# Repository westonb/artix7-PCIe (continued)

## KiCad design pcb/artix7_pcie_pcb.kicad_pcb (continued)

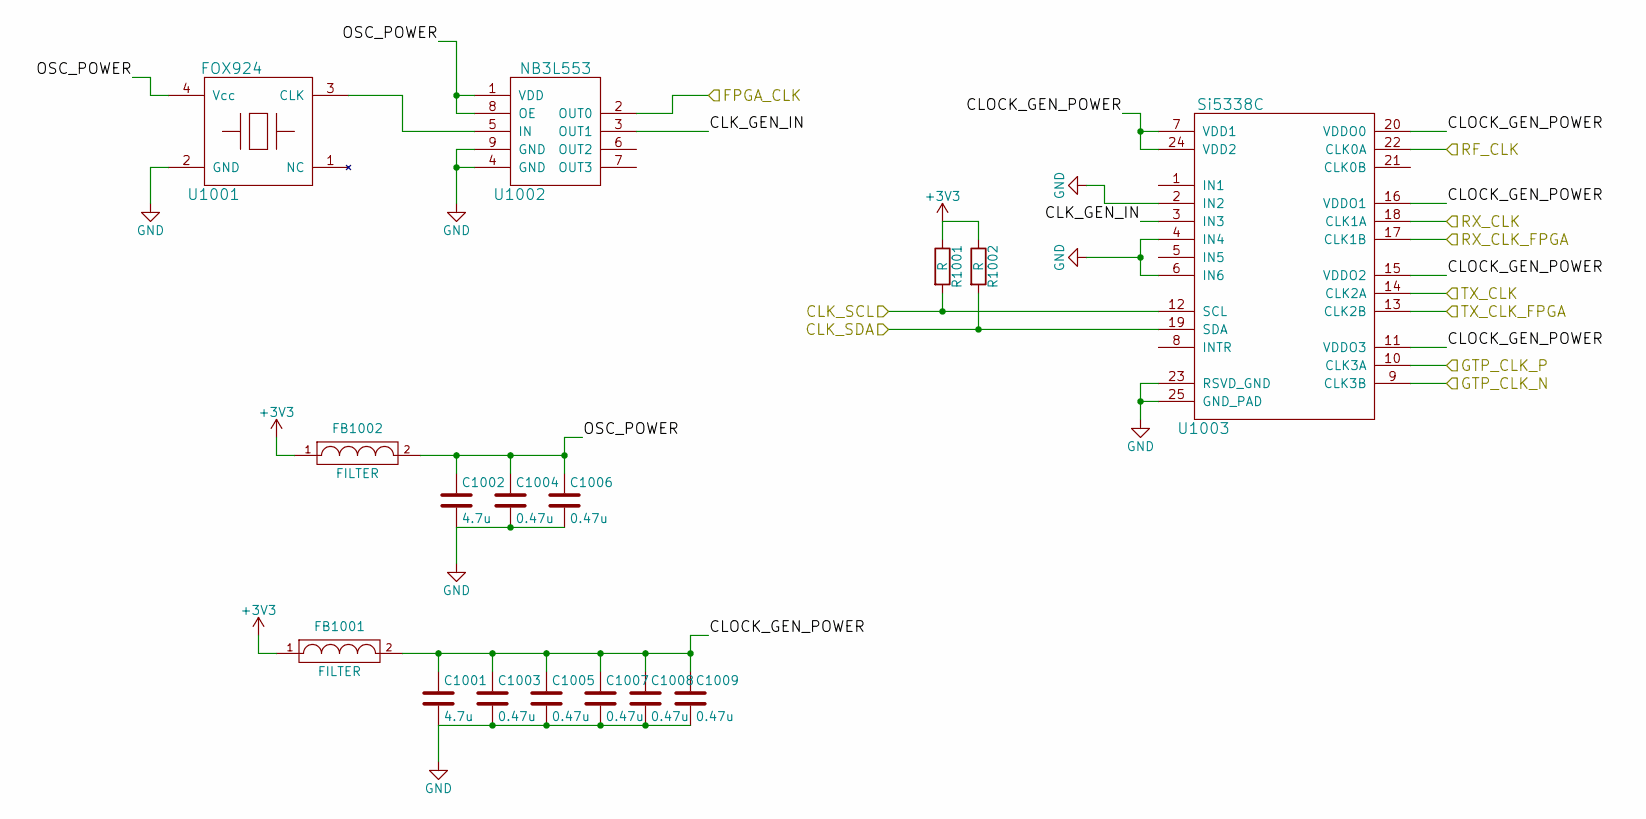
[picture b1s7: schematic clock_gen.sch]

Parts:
C1001, C1002: 4.7u; C_0402
C1003, C1004, C1005, C1006, C1007, C1008, C1009: 0.47u; C_0402
FB1001, FB1002: FILTER; L_0603
R1001, R1002: R; R_0402
U1001: FOX924; OSCILLATOR_5.0X3.2
U1002: NB3L553; DFN-8_2x2mm_Pitch0.5mm
U1003: Si5338C; QFN-24-1EP_4x4mm_Pitch0.5mm

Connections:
+3V3: FB1001.1, FB1002.1, R1001.1, R1002.1; also elsewhere on the board
/Clocking/CLK_GEN_IN: U1002.3 (OUT1), U1003.3 (IN3)
/Clocking/CLK_SCL: R1001.2, U1003.12 (SCL); also elsewhere on the board
/Clocking/CLK_SDA: R1002.2, U1003.19 (SDA); also elsewhere on the board
/Clocking/CLOCK_GEN_POWER: C1001.1, C1003.1, C1005.1, C1007.1, C1008.1, C1009.1, FB1001.2, U1003.7 (VDD1), U1003.11 (VDDO3), U1003.15 (VDDO2), U1003.16 (VDDO1), U1003.20 (VDDO0), U1003.24 (VDD2)
/Clocking/FPGA_CLK: U1002.2 (OUT0); also elsewhere on the board
/Clocking/GTP_CLK_N: U1003.9 (CLK3B); also elsewhere on the board
/Clocking/GTP_CLK_P: U1003.10 (CLK3A); also elsewhere on the board
/Clocking/OSC_POWER: C1002.1, C1004.1, C1006.1, FB1002.2, U1001.4 (Vcc), U1002.1 (VDD), U1002.8 (OE)
/Clocking/RF_CLK: U1003.22 (CLK0A); also elsewhere on the board
/Clocking/RX_CLK: U1003.18 (CLK1A); also elsewhere on the board
/Clocking/RX_CLK_FPGA: U1003.17 (CLK1B); also elsewhere on the board
/Clocking/TX_CLK: U1003.14 (CLK2A); also elsewhere on the board
/Clocking/TX_CLK_FPGA: U1003.13 (CLK2B); also elsewhere on the board
GND: C1001.2, C1002.2, C1003.2, C1004.2, C1005.2, C1006.2, C1007.2, C1008.2, C1009.2, U1001.2 (GND), U1002.4 (GND), U1002.9 (GND), U1003.2 (IN2), U1003.4 (IN4), U1003.6 (IN6), U1003.23 (RSVD_GND), U1003.25 (GND_PAD); also elsewhere on the board
unnamed: U1001.3 (CLK), U1002.5 (IN)

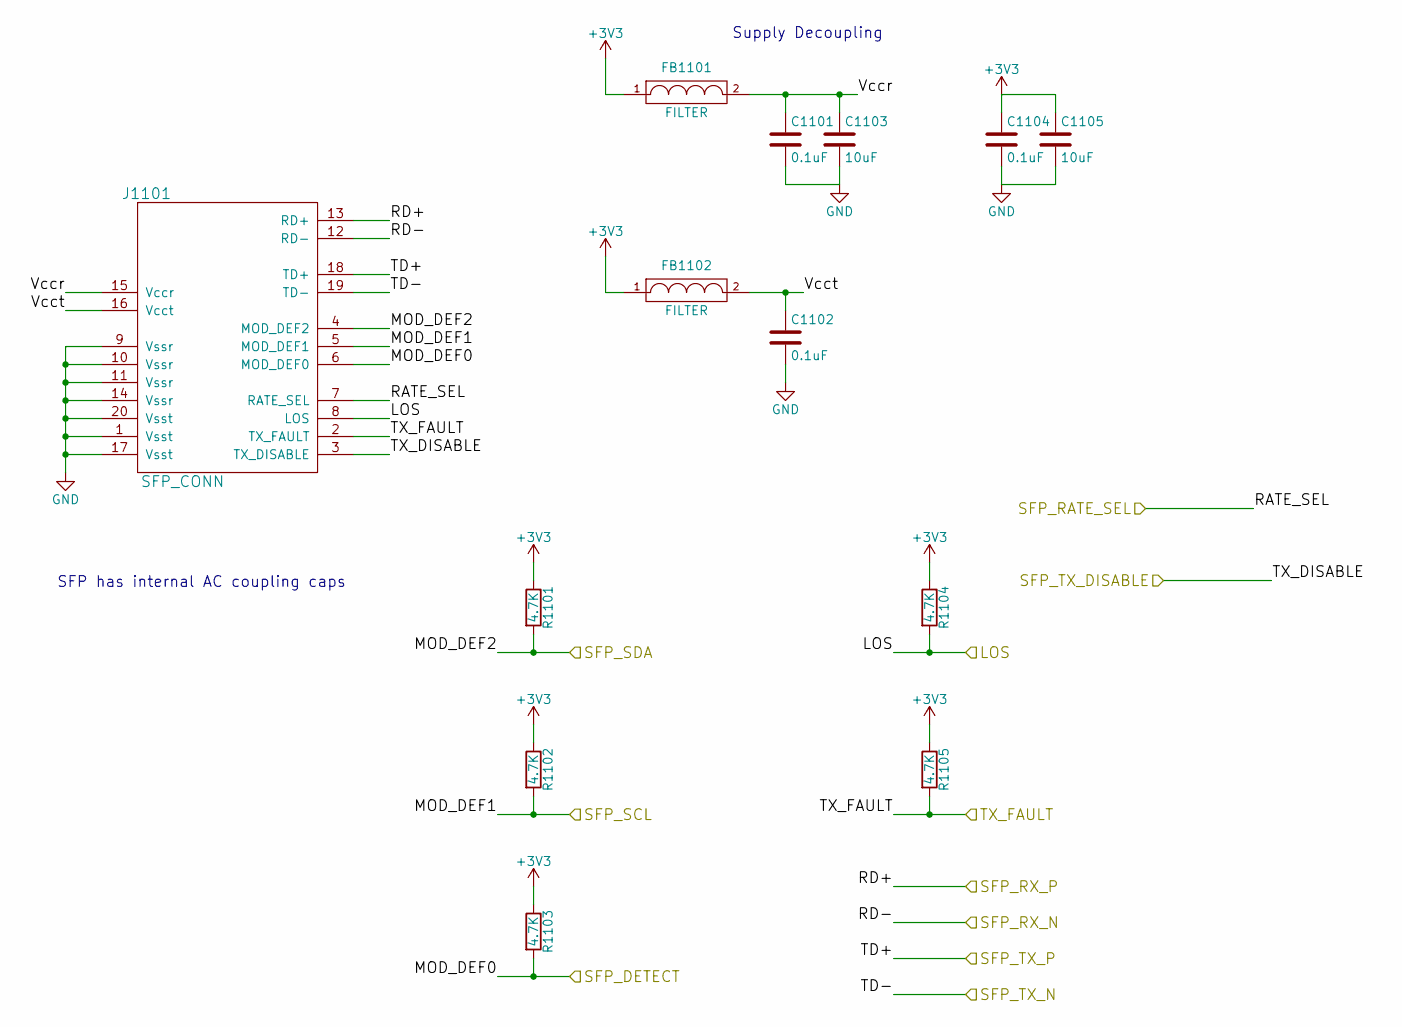
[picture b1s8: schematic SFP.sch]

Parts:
C1101, C1102, C1104: 0.1uF; C_0402
C1103, C1105: 10uF; C_0402
FB1101, FB1102: FILTER; L_0603
J1101: SFP_CONN; CONN-SFP_1367073-1
R1101, R1102, R1103, R1104, R1105: 4.7K; R_0402

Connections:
+3V3: C1104.1, C1105.1, FB1101.1, FB1102.1, R1101.1, R1102.1, R1103.1, R1104.1, R1105.1; also elsewhere on the board
/FPGA Transceivers/SFP_RX_N: J1101.12 (RD-); also elsewhere on the board
/FPGA Transceivers/SFP_RX_P: J1101.13 (RD+); also elsewhere on the board
/FPGA Transceivers/SFP_TX_N: J1101.19 (TD-); also elsewhere on the board
/FPGA Transceivers/SFP_TX_P: J1101.18 (TD+); also elsewhere on the board
/MyriadRF IO/SFP_DETECT: J1101.6 (MOD_DEF0), R1103.2; also elsewhere on the board
/MyriadRF IO/SFP_RATE_SEL: J1101.7 (RATE_SEL); also elsewhere on the board
/MyriadRF IO/SFP_SCL: J1101.5 (MOD_DEF1), R1102.2; also elsewhere on the board
/MyriadRF IO/SFP_SDA: J1101.4 (MOD_DEF2), R1101.2; also elsewhere on the board
/MyriadRF IO/SFP_TX_DISABLE: J1101.3 (TX_DISABLE); also elsewhere on the board
/MyriadRF IO/SFP_TX_FAULT: J1101.2 (TX_FAULT), R1105.2; also elsewhere on the board
/SFP/LOS: J1101.8 (LOS), R1104.2; also elsewhere on the board
/SFP/Vccr: C1101.1, C1103.1, FB1101.2, J1101.15 (Vccr)
/SFP/Vcct: C1102.1, FB1102.2, J1101.16 (Vcct)
GND: C1101.2, C1102.2, C1103.2, C1104.2, C1105.2, J1101.1 (Vsst), J1101.9 (Vssr), J1101.10 (Vssr), J1101.11 (Vssr), J1101.14 (Vssr), J1101.17 (Vsst), J1101.20 (Vsst); also elsewhere on the board

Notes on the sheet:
Supply Decoupling
SFP has internal AC coupling caps

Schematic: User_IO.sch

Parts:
D1201, D1202, D1203, D1204: LED; LED-0805
P1201, P1202: CONN_02X05; Pin_Header_Straight_2x05
R1201, R1202, R1203, R1204, R1207, R1208: R; R_0402
SW1201, SW1202: SW_PUSH; button-5mm
U401: XC7Axxt-FGG484; BGA_484_22x22_FULLARRAY_1MM

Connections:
+3V3: P1201.9, P1202.9, R1207.2, R1208.2; also elsewhere on the board
/User IO/B0: R1208.1, SW1202.1, U401.T1 (IO_L1P_T0_34)
/User IO/B1: R1207.1, SW1201.1, U401.U1 (IO_L1N_T0_34)
/User IO/IO0: P1201.1, U401.V4 (IO_L12P_T1_MRCC_34)
/User IO/IO1: P1201.2, U401.AA4 (IO_L11N_T1_SRCC_34)
/User IO/IO2: P1201.3, U401.Y4 (IO_L11P_T1_SRCC_34)
/User IO/IO3: P1201.4, U401.W4 (IO_L12N_T1_MRCC_34)
/User IO/IO4: P1201.5, U401.AB3 (IO_L8P_T1_34)
/User IO/IO5: P1201.6, U401.AA3 (IO_L9N_T1_DQS_34)
/User IO/IO6: P1201.7, U401.Y3 (IO_L9P_T1_DQS_34)
/User IO/IO7: P1201.8, U401.AB2 (IO_L8N_T1_34)
/User IO/IO8: P1202.1, U401.R4 (IO_L13P_T2_MRCC_34)
/User IO/IO9: P1202.2, U401.R3 (IO_L3P_T0_DQS_34)
/User IO/IO10: P1202.3, U401.AB1 (IO_L7N_T1_34)
/User IO/IO11: P1202.4, U401.AA1 (IO_L7P_T1_34)
/User IO/IO12: P1202.5, U401.Y2 (IO_L4N_T0_34)
/User IO/IO13: P1202.6, U401.Y1 (IO_L5N_T0_34)
/User IO/IO14: P1202.7, U401.W2 (IO_L4P_T0_34)
/User IO/IO15: P1202.8, U401.W1 (IO_L5P_T0_34)
/User IO/LED0: R1201.2, U401.U2 (IO_L2P_T0_34)
/User IO/LED1: R1202.2, U401.V2 (IO_L2N_T0_34)
/User IO/LED2: R1203.2, U401.U3 (IO_L6P_T0_34)
/User IO/LED3: R1204.2, U401.V3 (IO_L6N_T0_VREF_34)
/User IO/PCIE_PERST: U401.R6 (IO_L17P_T2_34); also elsewhere on the board
GND: D1201.1 (K), D1202.1 (K), D1203.1 (K), D1204.1 (K), P1201.10, P1202.10, SW1201.2, SW1202.2; also elsewhere on the board
unnamed: D1201.2 (A), R1201.1
unnamed: D1202.2 (A), R1202.1
unnamed: D1203.2 (A), R1203.1
unnamed: D1204.2 (A), R1204.1

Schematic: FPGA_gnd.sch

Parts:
U401: XC7Axxt-FGG484; BGA_484_22x22_FULLARRAY_1MM

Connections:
GND: U401.A2 (GND), U401.A3 (GND), U401.A5 (GND), U401.A7 (GND), U401.A9 (GND), U401.A11 (GND), U401.A12 (GND), U401.A22 (GND), U401.AA2 (GND), U401.AA12 (GND), U401.AA22 (GND), U401.AB9 (GND), U401.AB19 (GND), U401.B3 (GND), U401.B12 (GND), U401.B19 (GND), U401.C3 (GND), U401.C6 (GND), U401.C10 (GND), U401.C12 (GND), U401.C16 (GND), U401.D3 (GND), U401.D4 (GND), U401.D8 (GND), U401.D12 (GND), U401.D13 (GND), U401.E4 (GND), U401.E5 (GND), U401.E7 (GND), U401.E9 (GND), U401.E11 (GND), U401.E20 (GND), U401.F5 (GND), U401.F11 (GND), U401.F17 (GND), U401.G5 (GND), U401.G6 (GND), U401.G7 (GND), U401.G8 (GND), U401.G9 (GND), U401.G10 (GND), U401.G12 (GND), U401.G14 (GND), U401.H1 (GND), U401.H7 (GND), U401.H9 (GND), U401.H11 (GND), U401.H21 (GND), U401.J8 (GND), U401.J10 (GND), U401.J12 (GND), U401.J18 (GND), U401.K5 (GND), U401.K7 (GND), U401.K9 (GNDADC), U401.K11 (GND), U401.K15 (GND), U401.L2 (GND), U401.L8 (GND), U401.L22 (GND), U401.M7 (GND), U401.M11 (GND), U401.M19 (GND), U401.N6 (GND), U401.N8 (GND), U401.N16 (GND), U401.P3 (GND), U401.P7 (GND), U401.P9 (GND), U401.P11 (GND), U401.P13 (GND), U401.R8 (GND), U401.R10 (GND), U401.R12 (GND), U401.R20 (GND), U401.T7 (GND), U401.T9 (GND), U401.T11 (GND), U401.T17 (GND), U401.U4 (GND), U401.U14 (GND), U401.V1 (GND), U401.V11 (GND), U401.V21 (GND), U401.W8 (GND), U401.W18 (GND), U401.Y5 (GND), U401.Y15 (GND); also elsewhere on the board

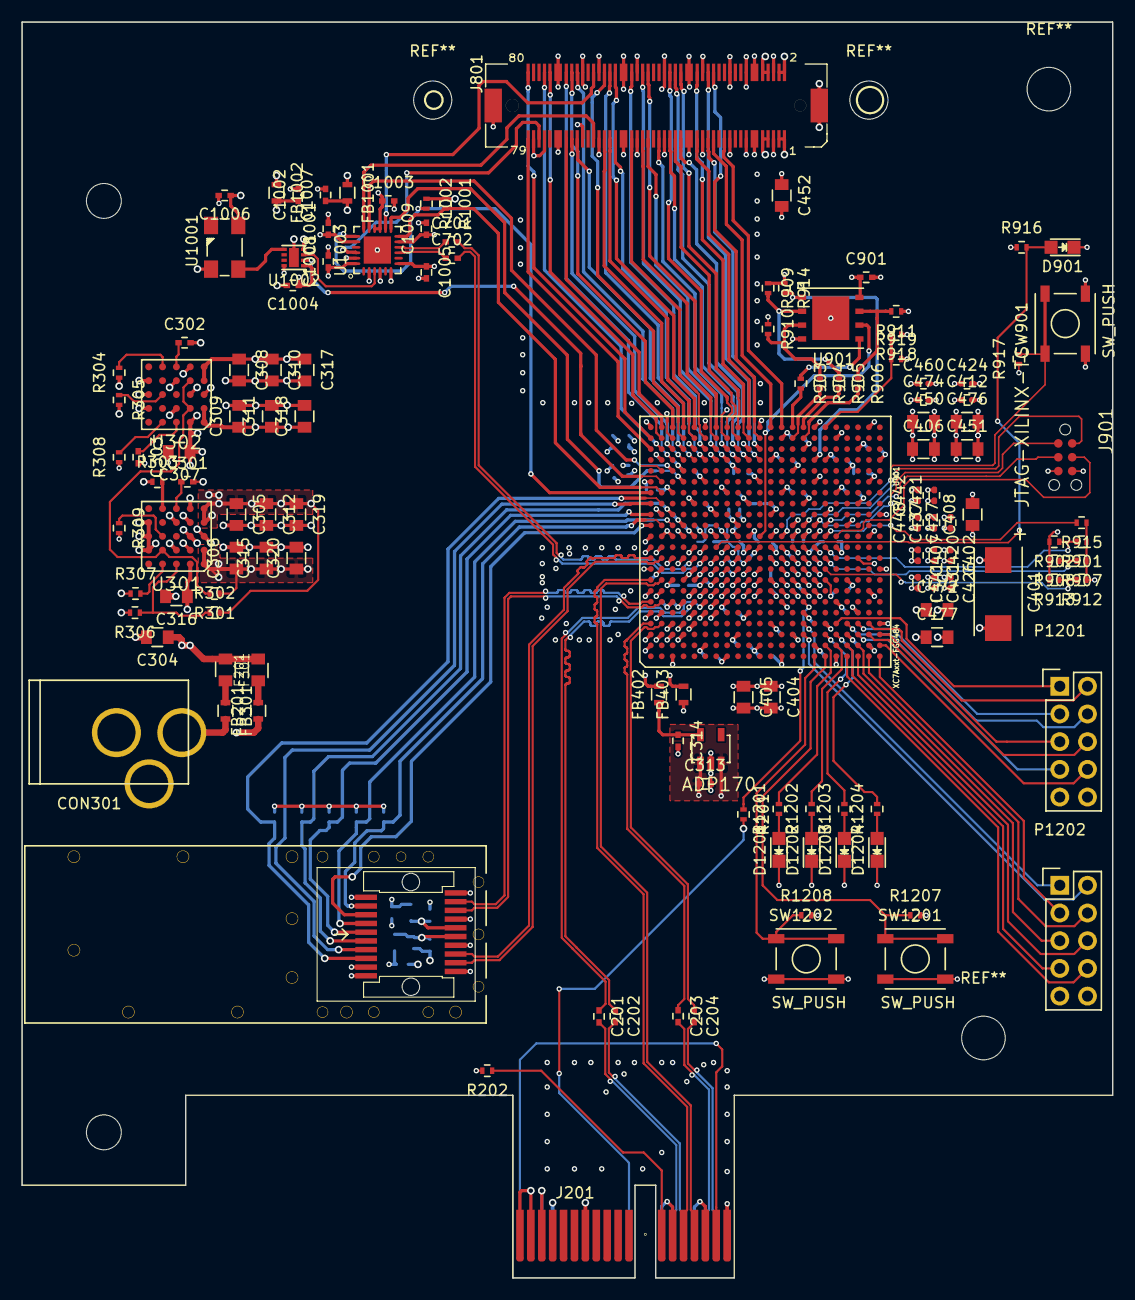
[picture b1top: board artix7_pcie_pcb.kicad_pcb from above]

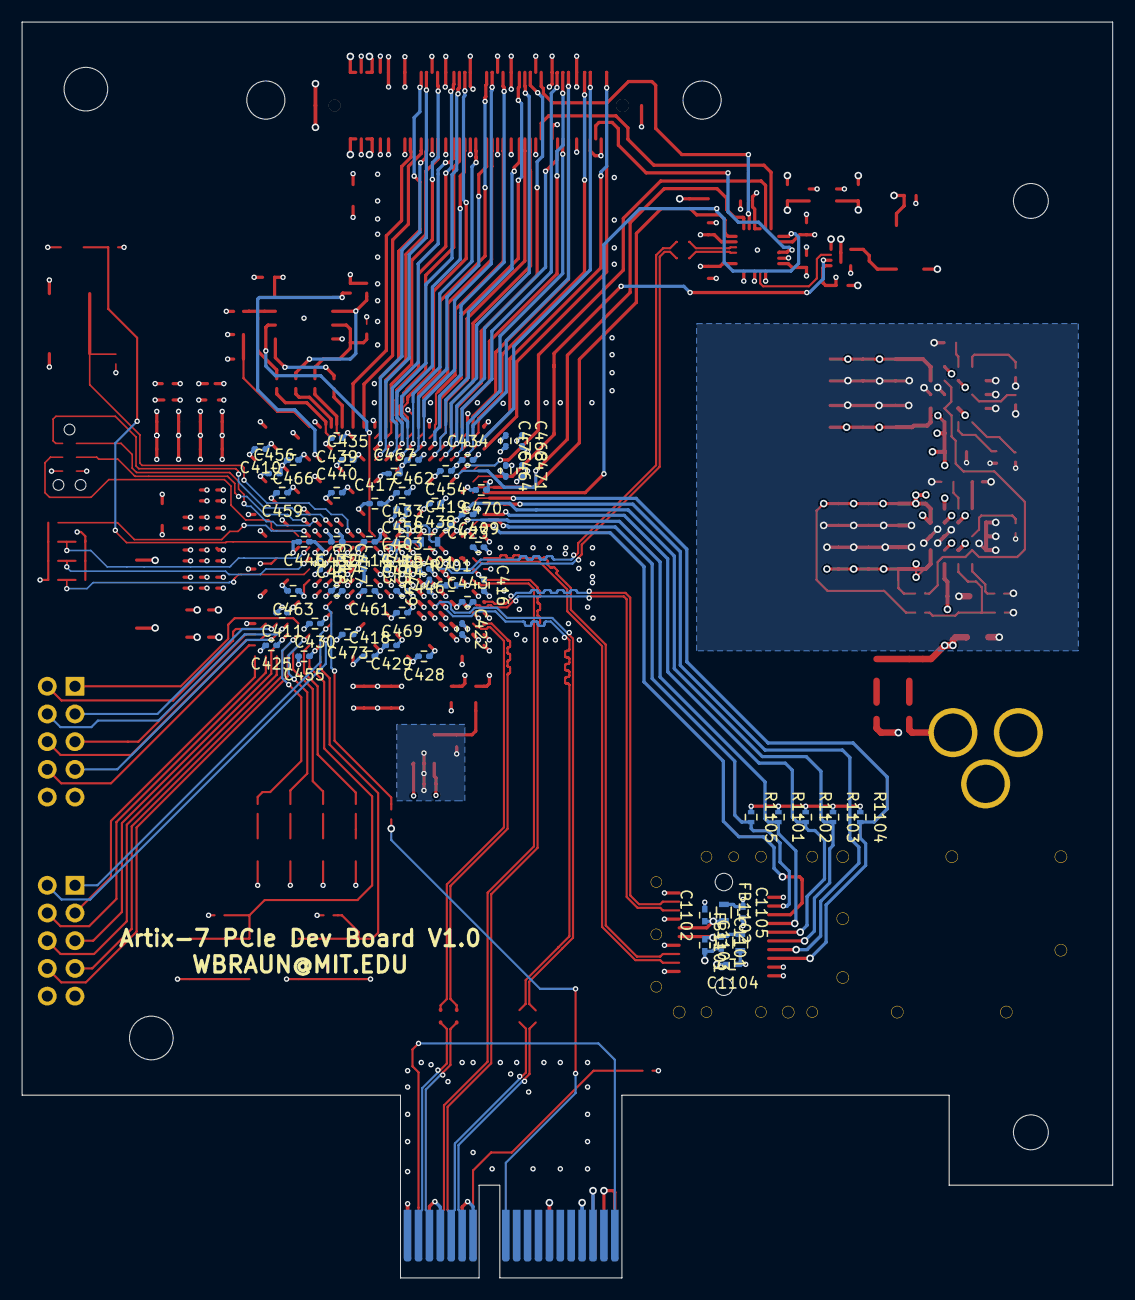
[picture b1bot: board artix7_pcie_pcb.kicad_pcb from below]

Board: 4 copper layers, 100.0 x 115.2 mm, 197 parts (65 on the bottom side), 152 nets.

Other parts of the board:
CONN-SFP-CAGE: VAL**; CONN-SFP-CAGE

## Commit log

2015-10-13 power pages done
2015-11-21 worked on configuration
2015-11-21 added new files
2015-12-03 schematic completed. Time for review
2015-12-03 Added part numbers and updated schematic
2015-12-05 mostly done with component placement
2015-12-06 Finished initial component placement
2015-12-07 DDR routing test 1
2015-12-21 Finished most of the routing, removed DDR-3
2015-12-22 power routing finished
2015-12-23 routing finished, need final check
2015-12-24 Pending final check
2015-12-24 Added PDFs of layout
2015-12-25 Ready for fab
2015-12-27 generated gerbers
2015-12-28 sent off PCB to fab
2015-12-28 sent of PCB to fab
2016-01-30 updated schematic, stencil
2017-09-27 updated project readme
